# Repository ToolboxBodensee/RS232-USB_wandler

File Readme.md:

# RS232-USB Wandler

**Entwicklung nur auf [GitLab](https://gitlab.com/ToolboxBodensee/microcontroller/RS232-USB_wandler). Auf GitHub befindet sich lediglich ein Mirror**

zum Anschlieen eines HC-06 Moduls am PC
Spannungsversorgung erfolgt wahlweise mit 5 oder 3v3(Whlbar ber Jumper-Widerstand)
Pegelwandler etc. sind vorhanden

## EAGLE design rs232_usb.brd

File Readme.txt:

RS232-USB Wandler

zum Anschließen eines HC-06 Moduls am PC
Spannungsversorgung erfolgt wahlweise mit 5 oder 3v3(Wählbar über Jumper-Widerstand)
Pegelwandler etc. sind vorhanden

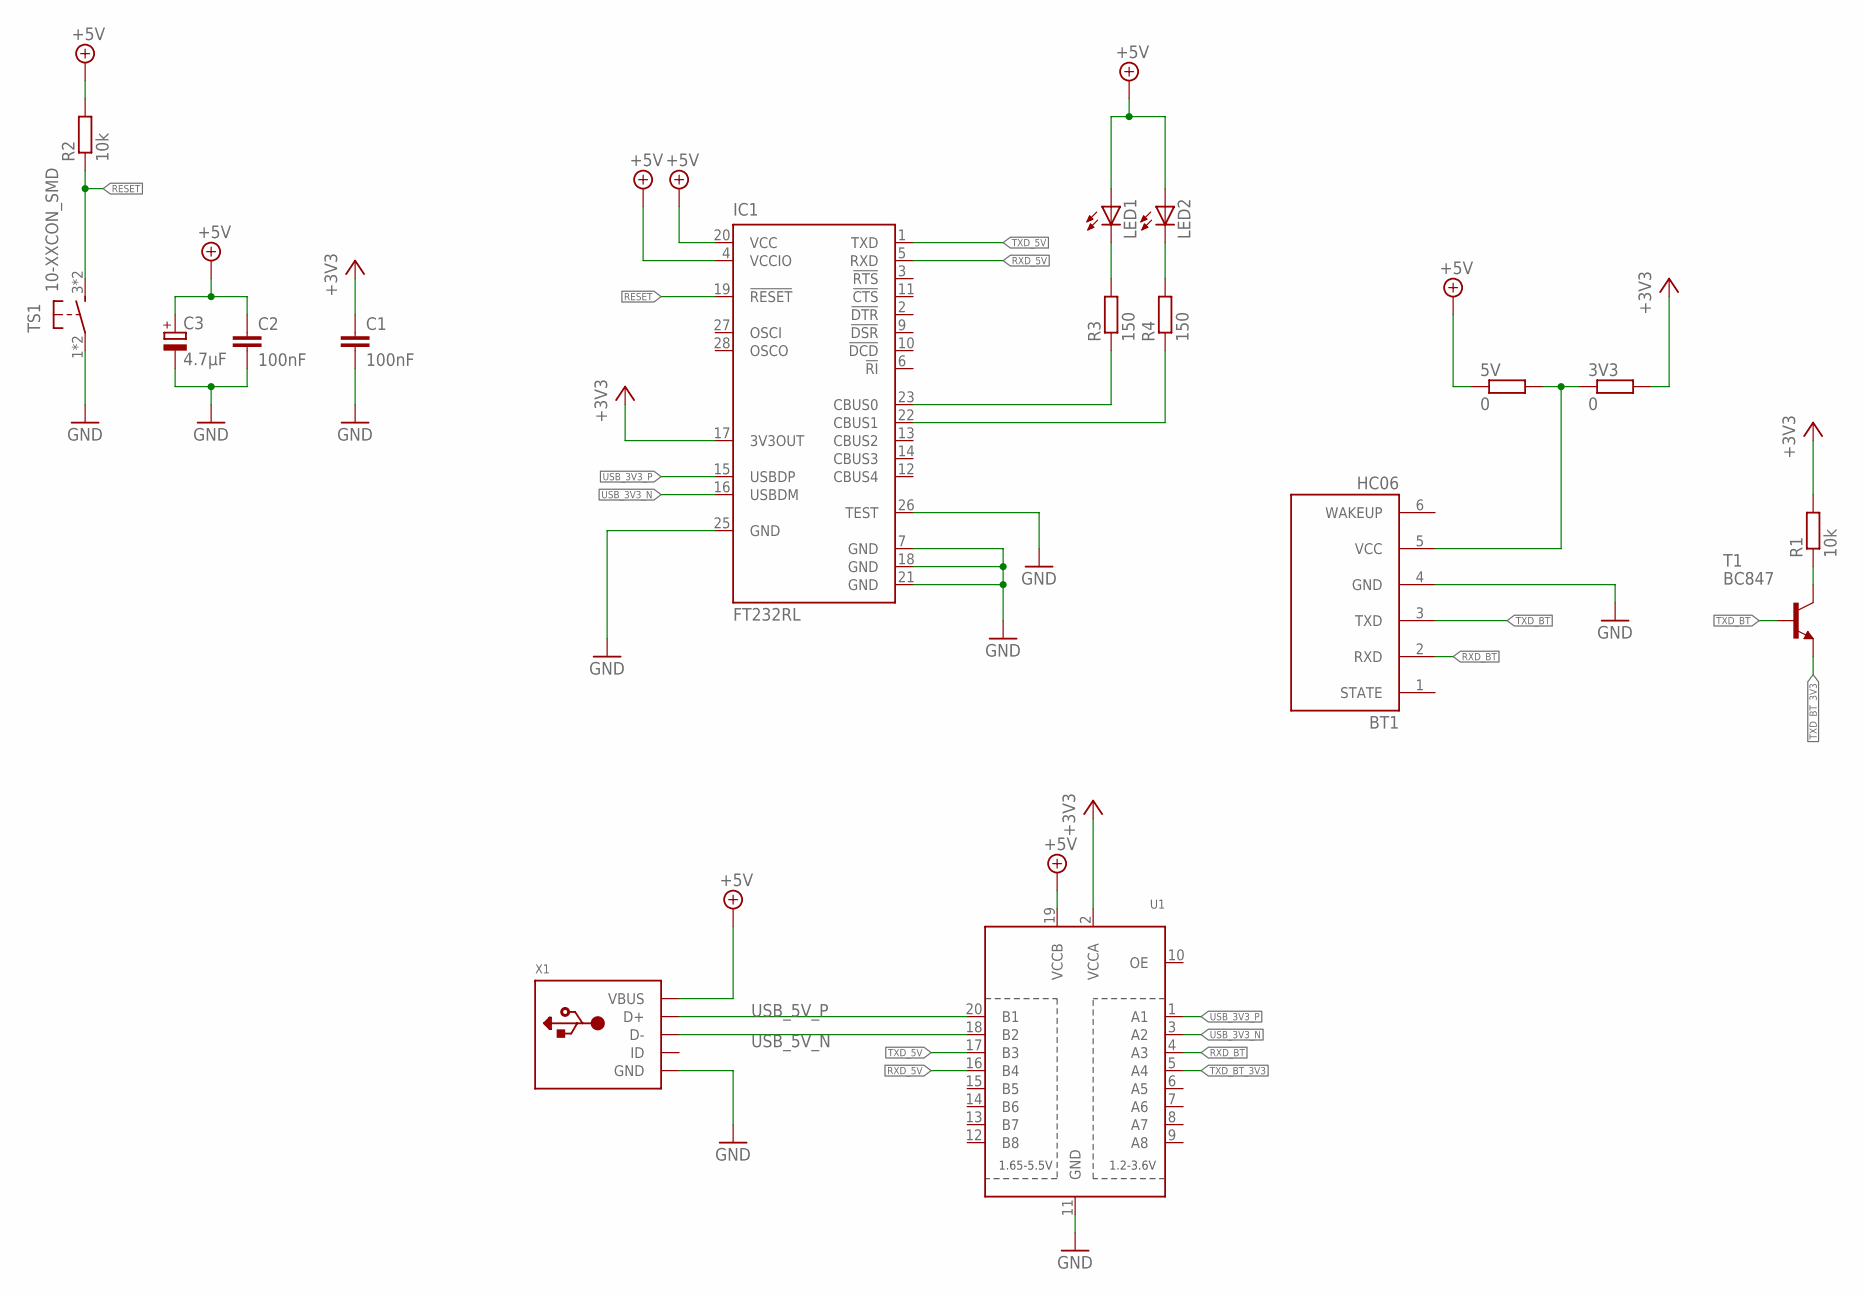
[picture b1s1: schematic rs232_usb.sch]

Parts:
3V3, 5V: 0; R0805
BT1: HC06
C1, C2: 100nF; C0805
C3: 4.7µF; C/6032-28R
IC1: FT232RL; SSOP28
LED1, LED2: LEDCHIPLED_0805; CHIPLED_0805
R1, R2: 10k; R0805
R3, R4: 150; R0805
T1: BC847; SOT23
TS1: 10-XXCON_SMD; SKHMPXE010
U1: TXB0108PWR; TSSOP20
X1: USBMINIB; USB-MINIB

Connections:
+3V3: 3V3.2, C1.1, IC1.17 (3V3OUT), R1.2, U1.2 (VCCA)
+5V: 5V.1, C2.1, C3.+, IC1.4 (VCCIO), IC1.20 (VCC), LED1.A, LED2.A, R2.2, U1.19 (VCCB), X1.VBUS
GND: BT1.4 (GND), C1.2, C2.2, C3.-, IC1.7 (GND), IC1.18 (GND), IC1.21 (GND), IC1.25 (GND), IC1.26 (TEST), TS1.1, TS1.2, U1.11 (GND), X1.GND
LED1: IC1.23 (CBUS0), R3.1
LED2: IC1.22 (CBUS1), R4.1
unnamed: 3V3.1, 5V.2, BT1.5 (VCC)
unnamed: LED1.C, R3.2
unnamed: LED2.C, R4.2
unnamed: R1.1, T1.3 (C)
RESET: IC1.19 (!RESET), R2.1, TS1.3 (S), TS1.4 (S)
RXD_5V: IC1.5 (RXD), U1.16 (B4)
RXD_BT: BT1.2 (RXD), U1.4 (A3)
TXD_5V: IC1.1 (TXD), U1.17 (B3)
TXD_BT: BT1.3 (TXD), T1.1 (B)
TXD_BT_3V3: T1.2 (E), U1.5 (A4)
USB_3V3_N: IC1.16 (USBDM), U1.3 (A2)
USB_3V3_P: IC1.15 (USBDP), U1.1 (A1)
USB_5V_N: U1.18 (B2), X1.D-
USB_5V_P: U1.20 (B1), X1.D+

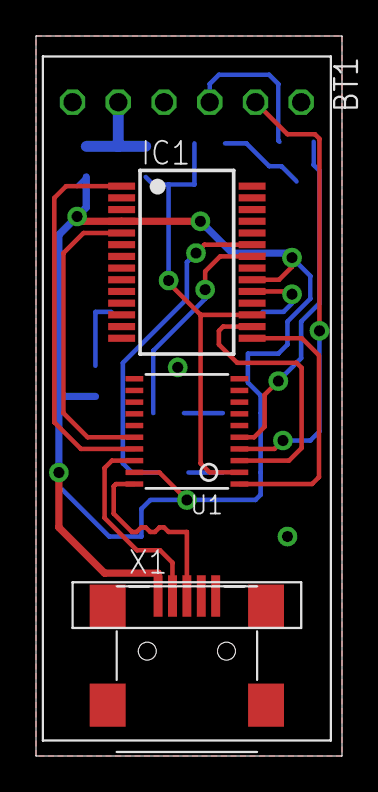
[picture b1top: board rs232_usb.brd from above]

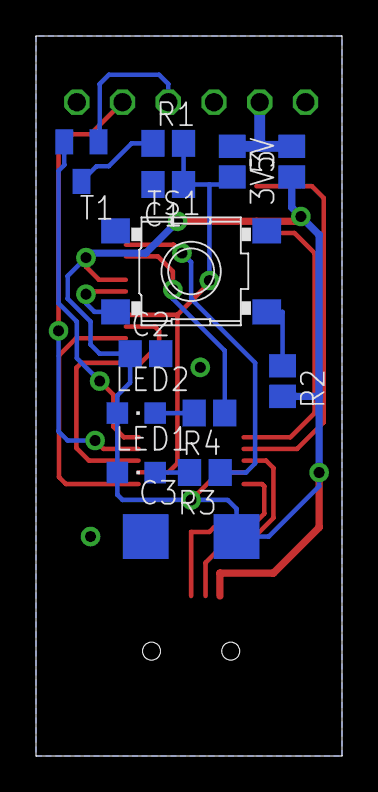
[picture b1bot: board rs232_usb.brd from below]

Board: 2 copper layers, 17.0 x 40.0 mm, 17 parts (13 on the bottom side), 19 nets.

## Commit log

2015-12-26 Schaltplan, Gitignore und erster Board Versuch(einseitig)
2015-12-29 1. Fertiges Layout (Beidseitig)
2015-12-31 added Readme
2019-11-28 add gitlab warning
